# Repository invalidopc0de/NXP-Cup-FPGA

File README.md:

# NXP Cup FPGA

## Overview

This project involved directing the NXP (Freescale) Cup Car to drive around a white track with two black lanes on each side.  This solution uses a Cyclone V SE SoC/FPGA with an OV7670 camera sensor to steer the car.  The FPGA side of the SoC is used to interface with the camera, apply filtering to the data stream, and finally hand the data over to the ARM CPU for processing in Linux.  The Linux application analyzes the data, determines which lines can be seen, and uses a PID loop to calculate motor control outputs.  These outputs are then communicated back to the FPGA, which controls the motors.  

## Project Directory Layout

**doc** - Project Documentation (Diagrams, Whitepapers, Datasheets)

**hw** - Hardware Schematics and PCBs

**ip** - Generated IP Cores (Altera MegaWizard)

**mech**  - Mechanical CAD models 

**prj** - Tool specific files (Quartus Project Files, etc)

**sim** - Simulations for Programmable Logic (Testbenches)

**src** - Source for Programmable Logic

**sw** - Software source code

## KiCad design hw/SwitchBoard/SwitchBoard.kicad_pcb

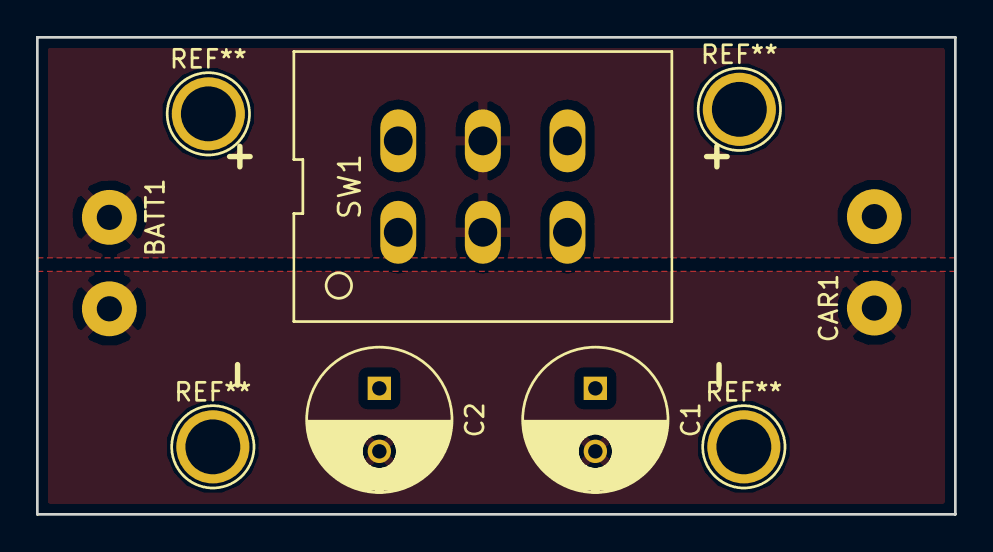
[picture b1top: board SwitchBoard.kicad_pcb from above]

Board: 2 copper layers, 51.0 x 26.5 mm, 5 parts (0 on the bottom side), 3 nets, no tracks yet.

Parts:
BATT1: CONN_01X02; terminal_block
C1, C2: 220uF; C_Radial_D8_L11.5_P3.5
CAR1: CONN_01X02; terminal_block
SW1: Switch_SPDT_x2; DIP-6_0_ELL

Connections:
unnamed: BATT1.1, C1.2, C2.2, CAR1.2
unnamed: BATT1.2, SW1.2, SW1.5
unnamed: C1.1, C2.1, CAR1.1, SW1.1, SW1.6

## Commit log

2016-11-09 Added VHDL for Sobel filter and Camera interfacing
2016-11-15 added latest FPGA/Qsys
2016-11-22 Updated files to include components
2016-11-24 First update to smoother
    Updated I/O, added state machine and primitive smoothing. Still have to run testbench and add gaussian smoothing
2016-11-24 Added smoother testbench and do file
2016-11-28 Camera FIFO driver model
2016-11-28 Added libev for control loop
2016-11-28 Added camera interface
2016-11-28 Added appnotes for the camera
2016-11-28 Added camera testbench
2016-11-29 Added 3D model for the camera mount
2016-11-30 Finished primary smoother test
2016-11-30 Updated do file for smoother testbench
2016-11-30 Working camera
2016-11-30 made files compile in 2008 VHDL
2016-12-01 Brought in numeric std and fixed compile errors
2016-12-01 Added component declaration and bug fixes
2016-12-01 Added JSON config
2016-12-01 Modified line search algorithm
2016-12-01 Added configs
2016-12-02 Line Analyzer changes
2016-12-02 Fixed backwards things
2016-12-02 Switched lines (they were backwards)
2016-12-02 Added a case for no edges
2016-12-02 Added a state to the line analyzer
2016-12-02 added a history enable
2016-12-02 added history and enable for history use
2016-12-02 Proportional control added
2016-12-02 Flipped the shift register (used to be backwards)
2016-12-02 Fixed some checks in if statements
2016-12-02 Changed line analyzer to ignore edges more correctly
2016-12-02 lots of logic fixes
2016-12-02 Started PID loop
2016-12-02 Latest PID changes
2016-12-02 Finished PID loop
2016-12-03 Uploading final configuration
2016-12-03 Added SwitchBoard hardware
2016-12-03 Added BaseBoard Design
2016-12-03 Adding extraneous lab stuff
2016-12-03 Moved PDFs to Git LFS
2016-12-03 Moving documentation around
2016-12-03 Organizing documentation
2016-12-03 Added Readme
2016-12-03 Removed libev and cJSON dumps, replaced with git submodules
2016-12-04 Added QSys component difinitions
2016-12-04 Fixed gitignore to allow Qsys component definitions
2016-12-04 Added another missing Qsys component declaration
2016-12-06 Added report and final configs
